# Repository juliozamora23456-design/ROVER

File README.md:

# ROVER
Autonomous rover that detects and follows colored objects using computer vision.

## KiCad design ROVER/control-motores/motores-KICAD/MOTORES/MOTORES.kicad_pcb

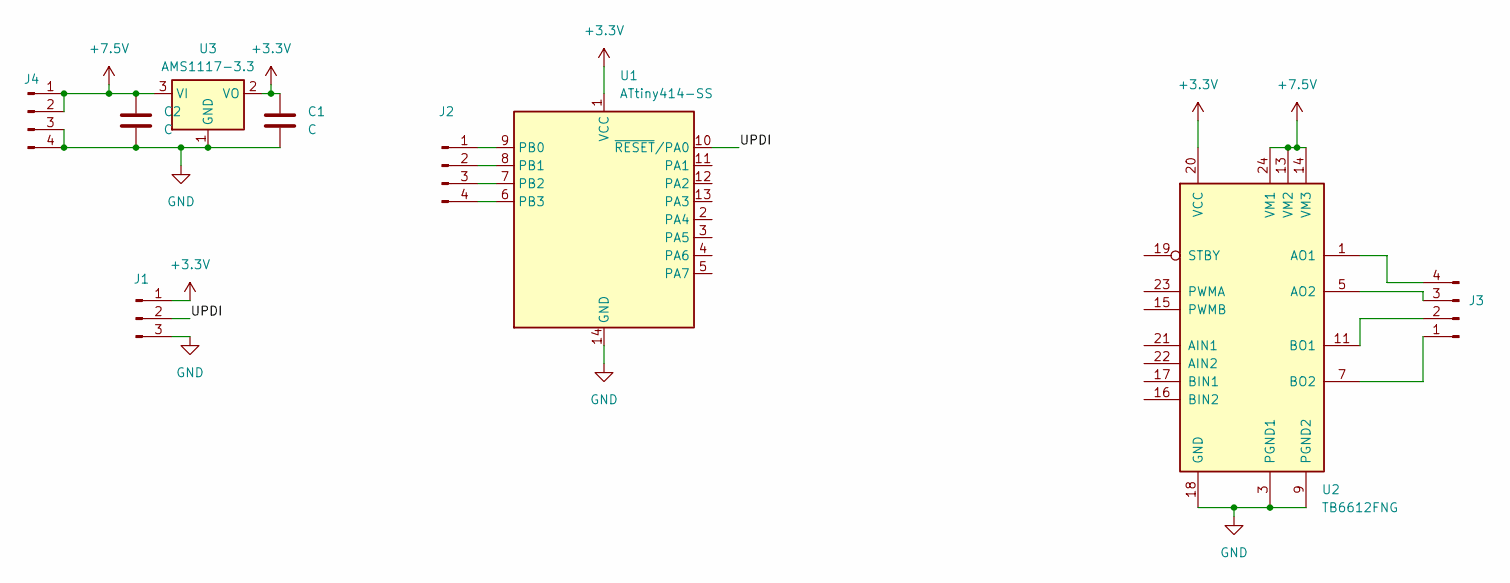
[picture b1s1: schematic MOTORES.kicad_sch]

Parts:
C1, C2: C; C_0805_2012Metric_Pad1.18x1.45mm_HandSolder
J1: Conn_01x03_Pin; PinSocket_1x03_P2.54mm_Vertical
J2, J3, J4: Conn_01x04_Pin; PinHeader_1x04_P2.54mm_Vertical
U1: ATtiny414-SS; SOIC-14_3.9x8.7mm_P1.27mm
U2: TB6612FNG; SSOP-24_5.3x8.2mm_P0.65mm
U3: AMS1117-3.3; SOT-223-3_TabPin2

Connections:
+3.3V: C1.1, J1.1, U1.1 (VCC), U2.20 (VCC), U3.2 (VO)
+7.5V: C2.2, J4.1, J4.2, U2.13 (VM2), U2.14 (VM3), U2.24 (VM1), U3.3 (VI)
/UPDI: J1.2, U1.10 (~RESET/PA0)
GND: C1.2, C2.1, J1.3, J4.3, J4.4, U1.14 (GND), U2.3 (PGND1), U2.4 (PGND1), U2.9 (PGND2), U2.10 (PGND2), U2.18 (GND), U3.1 (GND)
unnamed: J2.1, U1.9 (PB0)
unnamed: J2.2, U1.8 (PB1)
unnamed: J2.3, U1.7 (PB2)
unnamed: J2.4, U1.6 (PB3)
unnamed: J3.1, U2.7 (BO2), U2.8 (BO2)
unnamed: J3.2, U2.11 (BO1), U2.12 (BO1)
unnamed: J3.3, U2.5 (AO2), U2.6 (AO2)
unnamed: J3.4, U2.1 (AO1), U2.2 (AO1)

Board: 2 copper layers, 9 parts (3 on the bottom side), 12 nets, no tracks yet.
